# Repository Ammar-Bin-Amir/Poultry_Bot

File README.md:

# Poultry Bot

Poultry Bot is a major technological breakthrough for the poultry industry as it provides solution for utmost problems faced in a poultry farm. The purpose of poultry bot is to completely revolutionize the century old farming practices used till now by introducing the latest technology for 1,190 billion rupees turnover generating sector. The goal is to minimize the biosecurity risk to help improve the production. Further, assisting human to make more informed and better decisions. Poultry bot is an autonomous self-driven robot, monitoring several factors effecting on a poultry farm by implementing ROS and IoT along with LIDAR mapping.

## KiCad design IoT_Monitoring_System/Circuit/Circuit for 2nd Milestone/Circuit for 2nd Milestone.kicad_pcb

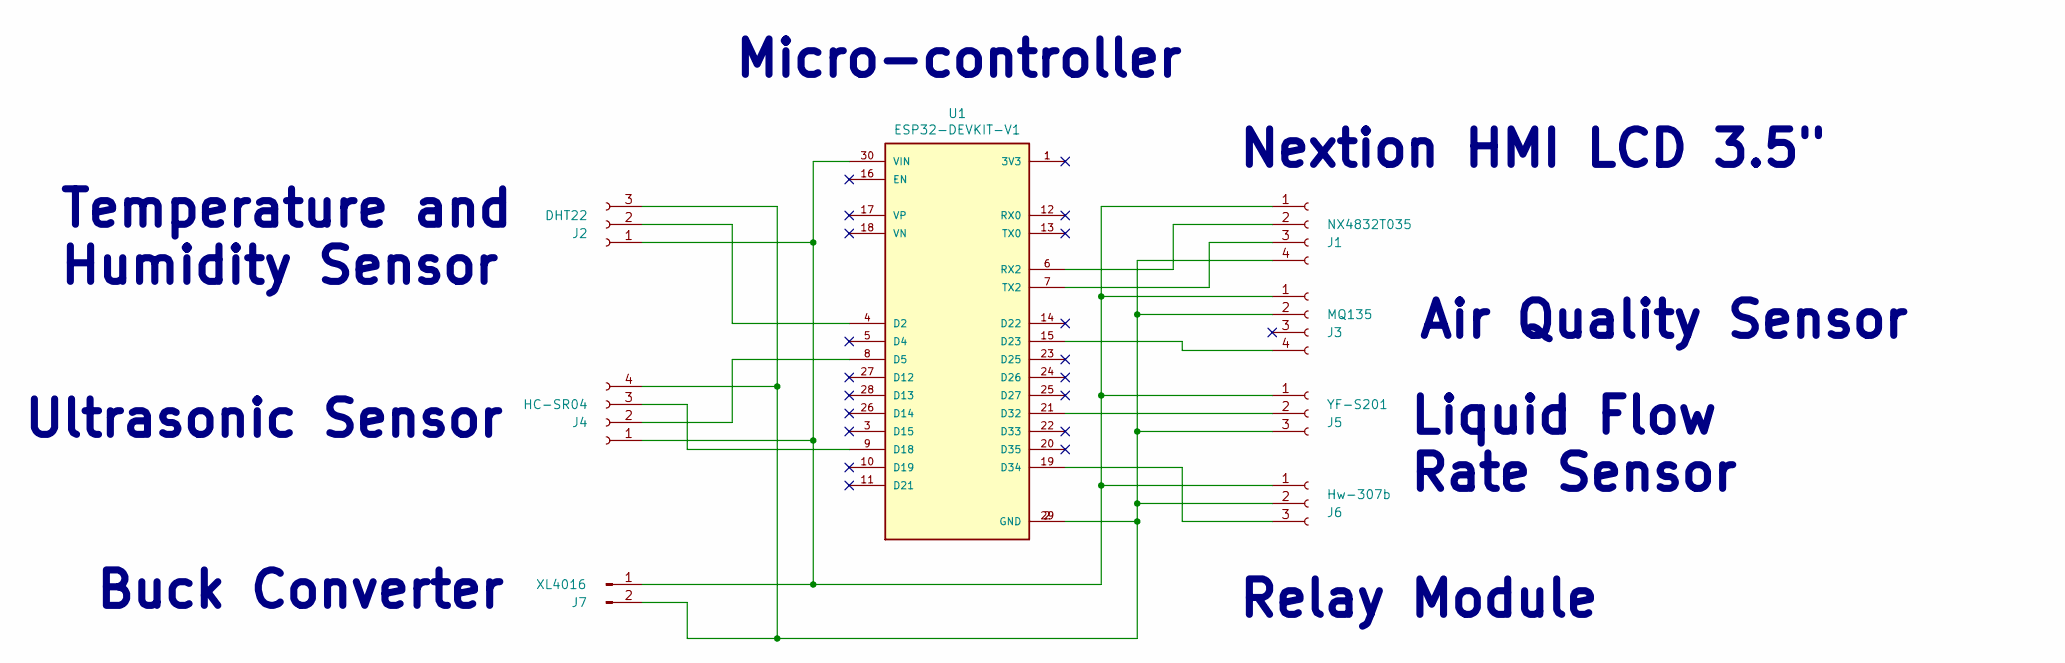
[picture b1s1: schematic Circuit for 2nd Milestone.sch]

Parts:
J1: NX4832T035; PinSocket_1x04_P2.54mm_Vertical
J2: DHT22; PinSocket_1x03_P2.54mm_Vertical
J3: MQ135; PinSocket_1x04_P2.54mm_Vertical
J4: HC-SR04; PinSocket_1x04_P2.54mm_Vertical
J5: YF-S201; PinSocket_1x03_P2.54mm_Vertical
J6: Hw-307b; PinSocket_1x03_P2.54mm_Vertical
J7: XL4016; PinHeader_1x02_P2.54mm_Vertical
U1: ESP32-DEVKIT-V1; MODULE_ESP32_DEVKIT_V1; PARTREV N/A

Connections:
5V: J1.1, J2.1, J3.1, J4.1, J5.1, J6.1, J7.1, U1.30 (VIN)
DHT22: J2.2, U1.4 (D2)
Echo: J4.3, U1.9 (D18)
GND: J1.4, J2.3, J3.2, J4.4, J5.3, J6.2, J7.2, U1.2 (GND), U1.29 (GND)
MQ135: J3.4, U1.15 (D23)
RX: J1.3, U1.7 (TX2)
Relay: J6.3, U1.19 (D34)
TX: J1.2, U1.6 (RX2)
Trigger: J4.2, U1.8 (D5)
YF-S201: J5.2, U1.21 (D32)

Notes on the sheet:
Ultrasonic Sensor
Micro-controller
Relay Module
Liquid Flow Rate Sensor
Air Quality Sensor
Temperature and Humidity Sensor
Nextion HMI LCD 3.5"
Buck Converter

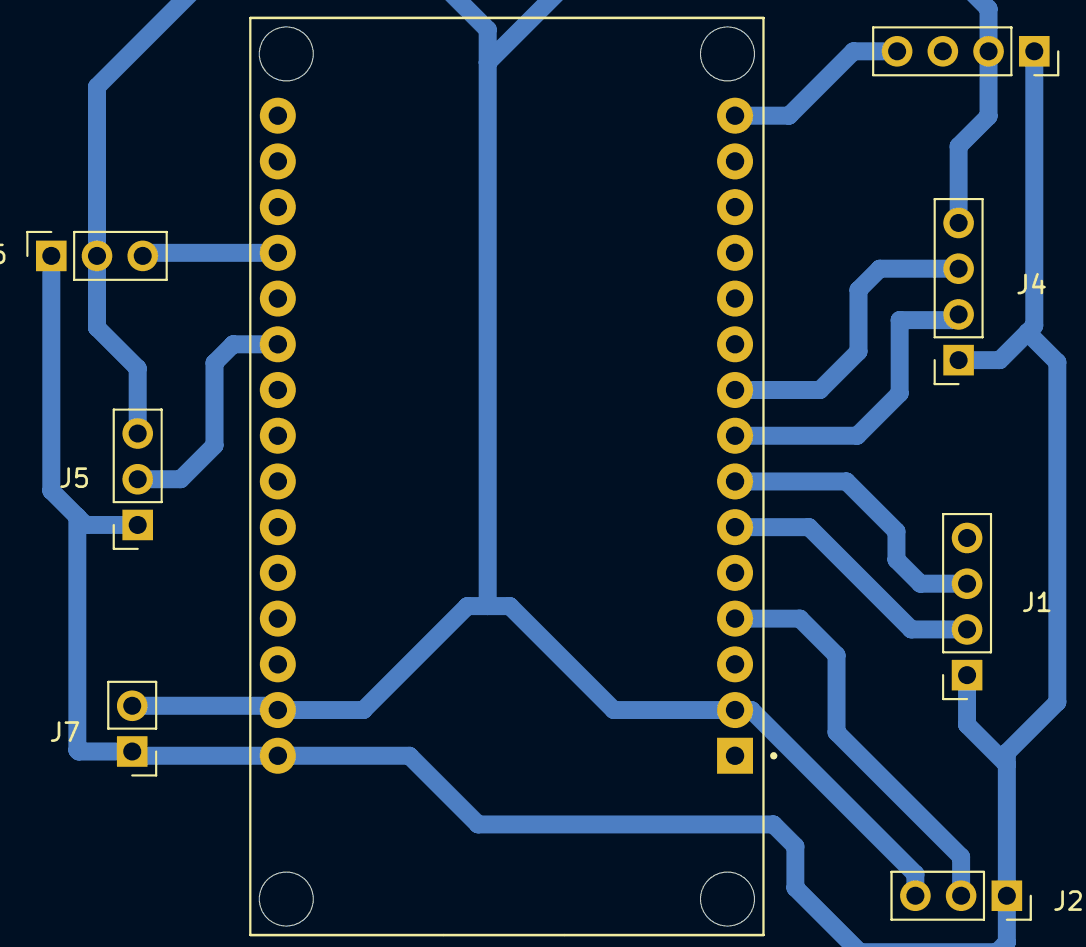
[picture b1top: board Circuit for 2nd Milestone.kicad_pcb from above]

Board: 2 copper layers, 8 parts (0 on the bottom side), 10 nets.

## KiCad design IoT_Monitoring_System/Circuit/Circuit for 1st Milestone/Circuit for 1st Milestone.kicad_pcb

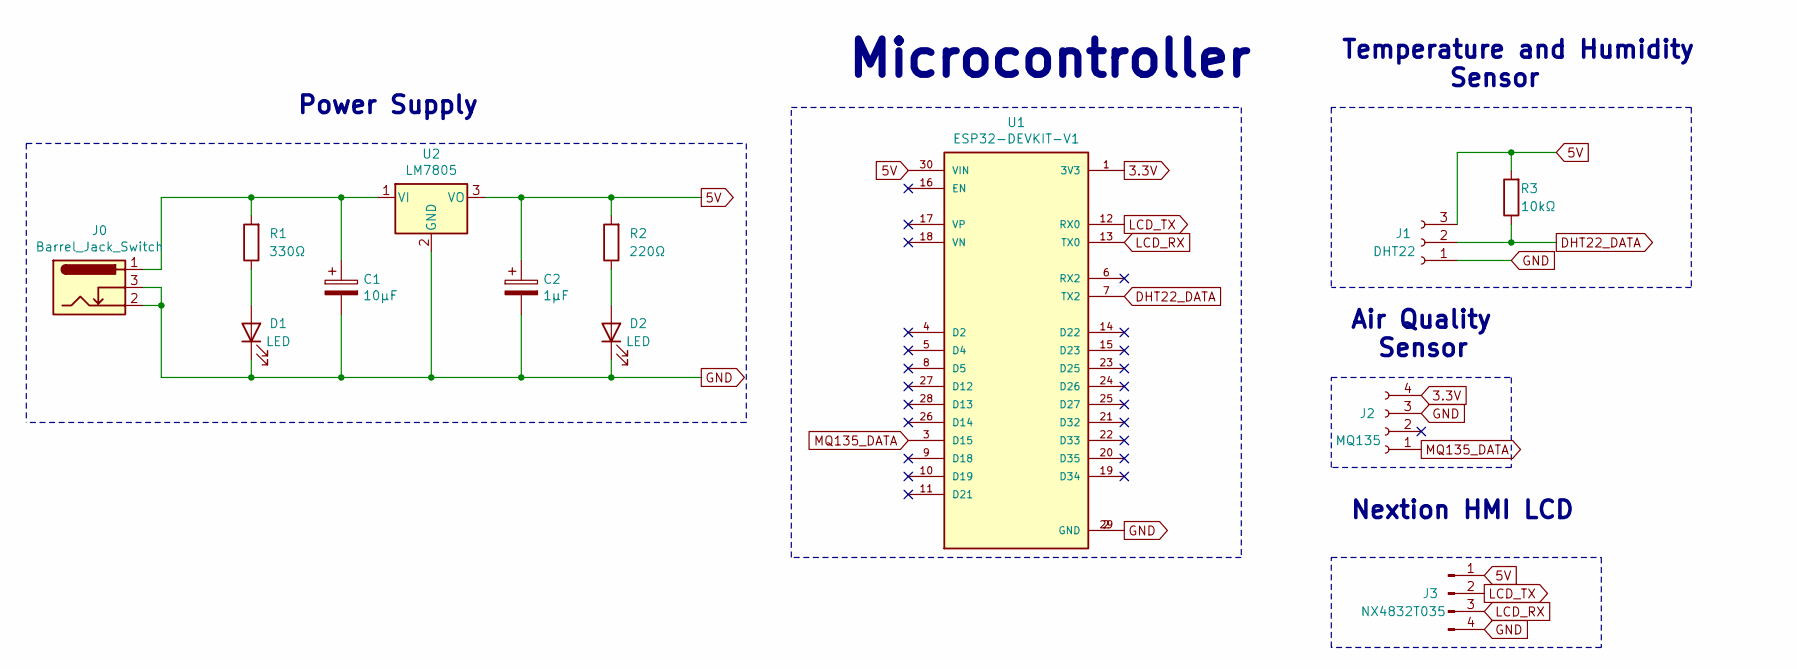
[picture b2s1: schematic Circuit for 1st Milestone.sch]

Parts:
C1: 10μF; CP_Radial_D6.3mm_P2.50mm
C2: 1μF; CP_Radial_D6.3mm_P2.50mm
D1, D2: LED; LED_D5.0mm_Clear
J0: Barrel_Jack_Switch; BarrelJack_Horizontal
J1: DHT22; PinSocket_1x03_P2.54mm_Vertical
J2: MQ135; PinSocket_1x04_P2.54mm_Vertical
J3: NX4832T035; PinHeader_1x04_P2.54mm_Vertical
R1: 330Ω; R_Axial_DIN0207_L6.3mm_D2.5mm_P10.16mm_Horizontal
R2: 220Ω; R_Axial_DIN0207_L6.3mm_D2.5mm_P10.16mm_Horizontal
R3: 10kΩ; R_Axial_DIN0207_L6.3mm_D2.5mm_P10.16mm_Horizontal
U1: ESP32-DEVKIT-V1; MODULE_ESP32_DEVKIT_V1; PARTREV N/A
U2: LM7805; TO-220-3_Vertical

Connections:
3.3V: J2.4, U1.1 (3V3)
5V: C2.1, J1.3, J3.1, R2.2, R3.2, U1.30 (VIN), U2.3 (VO)
DHT22_DATA: J1.2, R3.1, U1.7 (TX2)
GND: C1.2, C2.2, D1.1 (K), D2.1 (K), J0.2, J0.3, J1.1, J2.3, J3.4, U1.2 (GND), U1.29 (GND), U2.2 (GND)
LCD_RX: J3.3, U1.13 (TX0)
LCD_TX: J3.2, U1.12 (RX0)
MQ135_DATA: J2.1, U1.3 (D15)
unnamed: C1.1, J0.1, R1.2, U2.1 (VI)
unnamed: D1.2 (A), R1.1
unnamed: D2.2 (A), R2.1

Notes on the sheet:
Temperature and Humidity Sensor
Air Quality Sensor
Nextion HMI LCD
Power Supply
Microcontroller

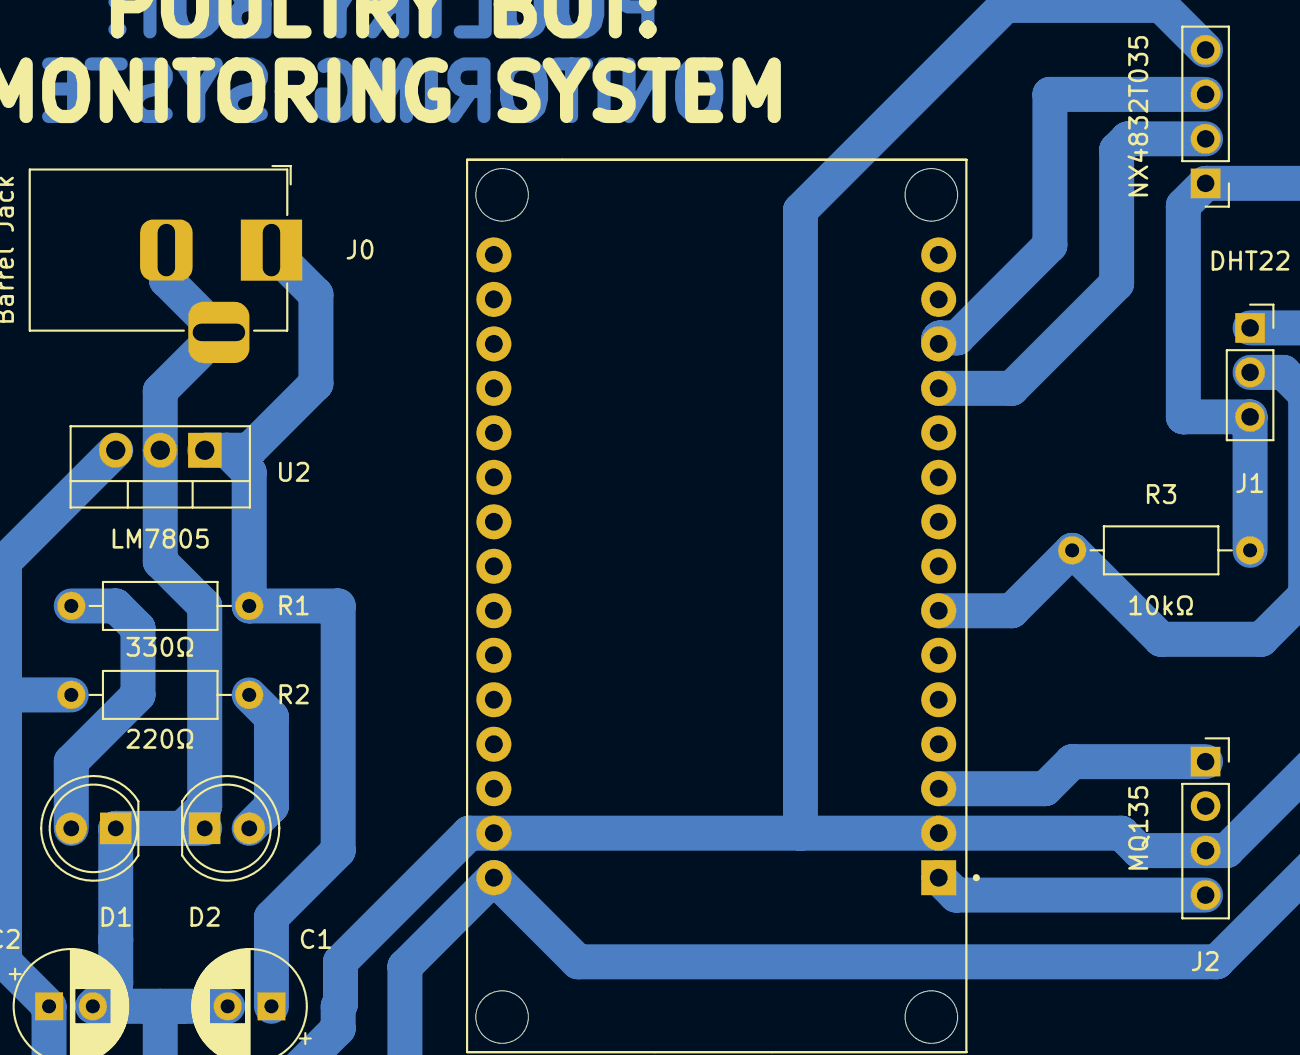
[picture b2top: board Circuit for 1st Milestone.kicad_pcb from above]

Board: 2 copper layers, 13 parts (0 on the bottom side), 10 nets.

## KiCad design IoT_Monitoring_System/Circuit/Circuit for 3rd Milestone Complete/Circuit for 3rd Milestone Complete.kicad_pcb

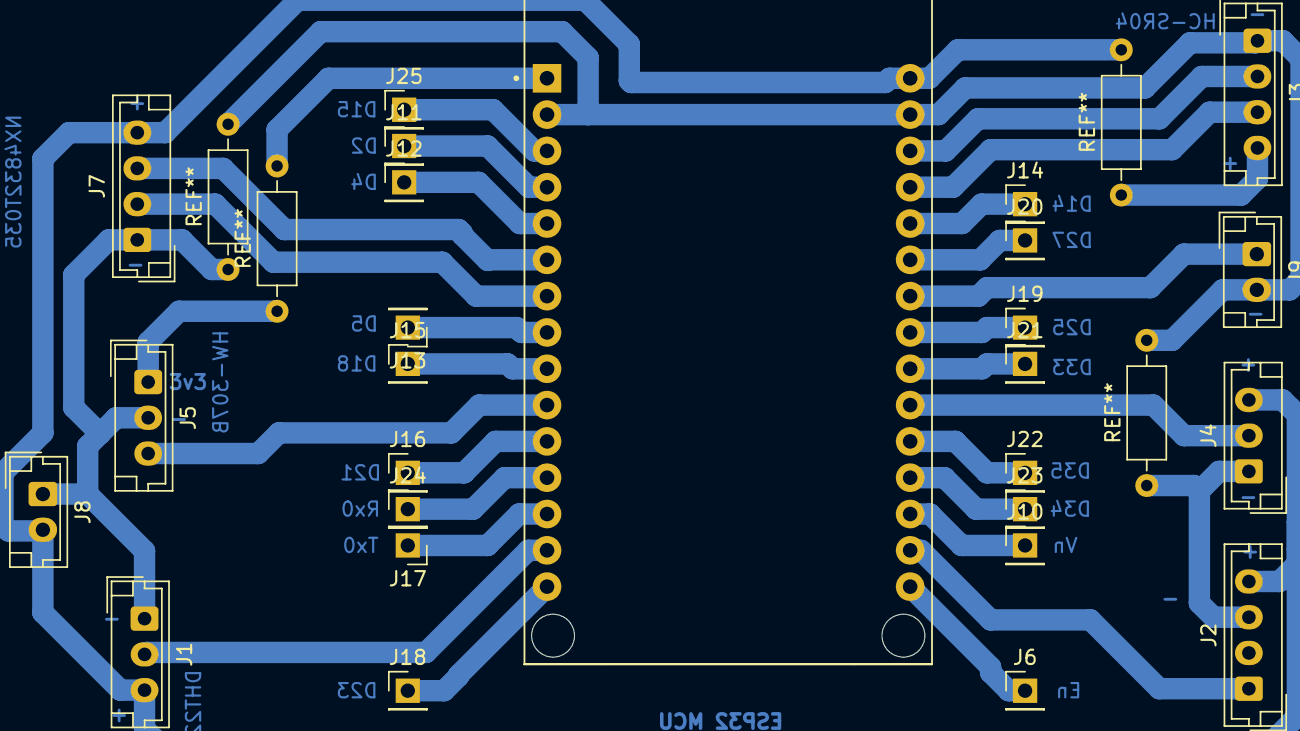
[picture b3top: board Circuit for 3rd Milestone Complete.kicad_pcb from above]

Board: 2 copper layers, 26 parts (0 on the bottom side), 29 nets.

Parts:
J1: DHT22; JST_EH_B3B-EH-A_1x03_P2.50mm_Vertical
J2: MQ135; JST_EH_B4B-EH-A_1x04_P2.50mm_Vertical
J3: HC-SR04; JST_EH_B4B-EH-A_1x04_P2.50mm_Vertical
J4: YF-S201; JST_EH_B3B-EH-A_1x03_P2.50mm_Vertical
J5: HW-307B; JST_EH_B3B-EH-A_1x03_P2.50mm_Vertical
J6: En; PinHeader_1x01_P2.54mm_Vertical
J7: NX4832T035; JST_EH_B4B-EH-A_1x04_P2.50mm_Vertical
J8: XL4016; JST_EH_B2B-EH-A_1x02_P2.50mm_Vertical
J9: Litter Raking; JST_EH_B2B-EH-A_1x02_P2.50mm_Vertical
J10: Vn; PinHeader_1x01_P2.54mm_Vertical
J11: D2; PinHeader_1x01_P2.54mm_Vertical
J12: D4; PinHeader_1x01_P2.54mm_Vertical
J13: D5; PinHeader_1x01_P2.54mm_Vertical
J14: D14; PinHeader_1x01_P2.54mm_Vertical
J15: D18; PinHeader_1x01_P2.54mm_Vertical
J16: D21; PinHeader_1x01_P2.54mm_Vertical
J17: Tx0; PinHeader_1x01_P2.54mm_Vertical
J18: D23; PinHeader_1x01_P2.54mm_Vertical
J19: D25; PinHeader_1x01_P2.54mm_Vertical
J20: D27; PinHeader_1x01_P2.54mm_Vertical
J21: D33; PinHeader_1x01_P2.54mm_Vertical
J22: D35; PinHeader_1x01_P2.54mm_Vertical
J23: D34; PinHeader_1x01_P2.54mm_Vertical
J24: Rx0; PinHeader_1x01_P2.54mm_Vertical
J25: D15; PinHeader_1x01_P2.54mm_Vertical
U1: ESP32 MCU; MODULE_ESP32_DEVKIT_V1

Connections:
unnamed: J2.1, U1.17 (VP)
unnamed: J1.1, J2.3, J3.1, J4.1, J5.2, J7.1, J8.1, J9.2, U1.2 (GND), U1.29 (GND)
unnamed: J1.3, J2.4, J3.4, J4.3, J7.4, J8.2, U1.30 (VIN)
unnamed: J4.2, U1.21 (D32)
unnamed: J5.1, U1.1 (3V3)
unnamed: J25.1, U1.3 (D15)
unnamed: J11.1, U1.4 (D2)
unnamed: J12.1, U1.5 (D4)
unnamed: J7.3, U1.6 (RX2)
unnamed: J7.2, U1.7 (TX2)
unnamed: J13.1, U1.8 (D5)
unnamed: J15.1, U1.9 (D18)
unnamed: J5.3, U1.10 (D19)
unnamed: J16.1, U1.11 (D21)
unnamed: J24.1, U1.12 (RX0)
unnamed: J17.1, U1.13 (TX0)
unnamed: J1.2, U1.14 (D22)
unnamed: J18.1, U1.15 (D23)
unnamed: J6.1, U1.16 (EN)
unnamed: J10.1, U1.18 (VN)
unnamed: J23.1, U1.19 (D34)
unnamed: J22.1, U1.20 (D35)
unnamed: J21.1, U1.22 (D33)
unnamed: J19.1, U1.23 (D25)
unnamed: J9.1, U1.24 (D26)
unnamed: J20.1, U1.25 (D27)
unnamed: J14.1, U1.26 (D14)
unnamed: J3.3, U1.27 (D12)
unnamed: J3.2, U1.28 (D13)

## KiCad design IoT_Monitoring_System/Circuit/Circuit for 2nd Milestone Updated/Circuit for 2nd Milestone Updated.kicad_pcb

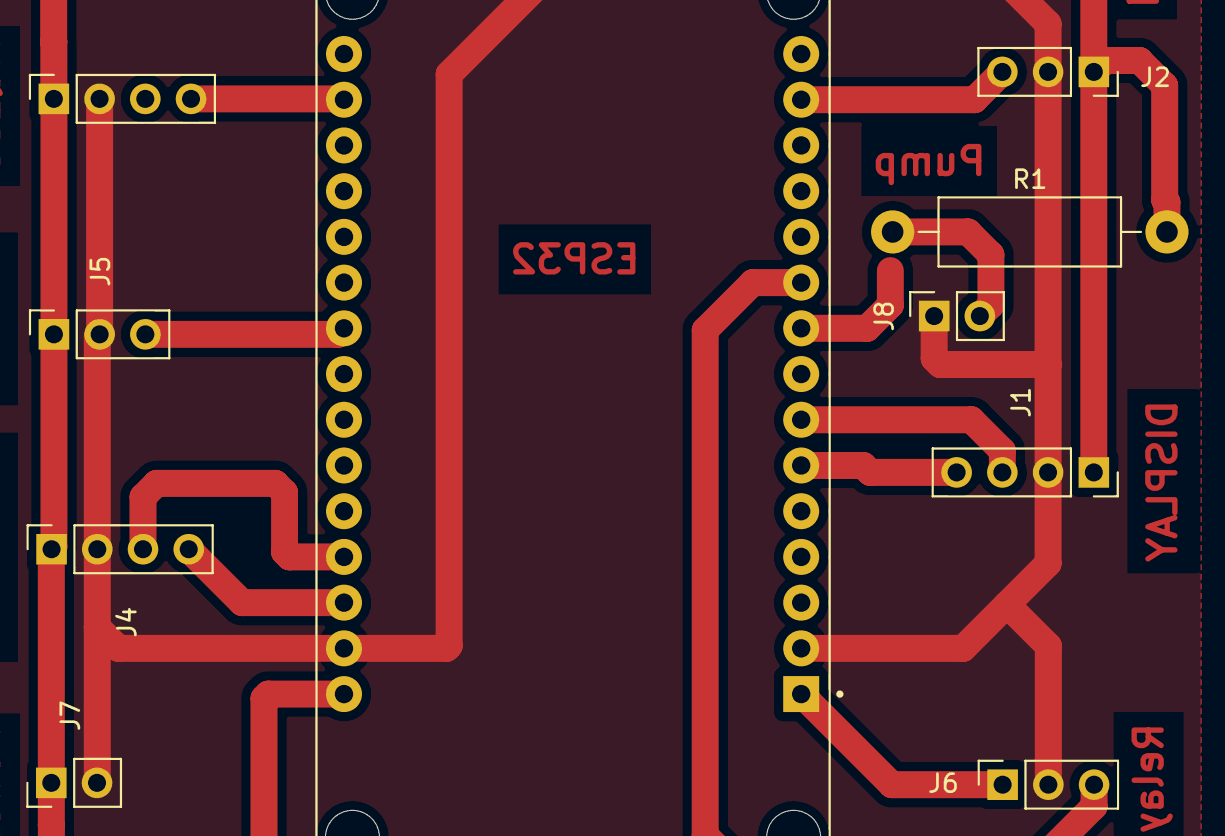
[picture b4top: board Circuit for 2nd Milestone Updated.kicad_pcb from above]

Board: 2 copper layers, 10 parts (0 on the bottom side), 7 nets.

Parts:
J1: NX4832T035; PinSocket_1x04_P2.54mm_Vertical
J2: DHT22; PinSocket_1x03_P2.54mm_Vertical
J3: MQ135; PinSocket_1x04_P2.54mm_Vertical
J4: HC-SR04; PinSocket_1x04_P2.54mm_Vertical
J5: YF-S201; PinSocket_1x03_P2.54mm_Vertical
J6: Hw-307b; PinSocket_1x03_P2.54mm_Vertical
J7: XL4016; PinHeader_1x02_P2.54mm_Vertical
J8: Pump Input; PinSocket_1x02_P2.54mm_Vertical
R1: R; R_Axial_DIN0411_L9.9mm_D3.6mm_P15.24mm_Horizontal
U1: ESP32-DEVKIT-V1; MODULE_ESP32_DEVKIT_V1

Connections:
unnamed: J1.1, J2.1, J3.1, J4.1, J5.1, J7.1, R1.2
unnamed: J1.2, J2.2, J3.2, J4.2, J5.2, J6.2, J7.2, J8.1
unnamed: U1.2 (GND), U1.29 (GND)
unnamed: J3.4, U1.17 (VP)
unnamed: J6.1, U1.1 (3V3)
unnamed: J6.3, U1.10 (D19)
unnamed: J8.2, R1.1

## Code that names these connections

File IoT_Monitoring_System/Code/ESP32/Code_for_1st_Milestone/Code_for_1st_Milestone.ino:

#include <WiFi.h>
#include <WiFiClient.h>
#include <BlynkSimpleEsp32.h>


#define BLYNK_TEMPLATE_ID "TMPLqo4MJG8x"
#define BLYNK_DEVICE_NAME "IoT"
#define BLYNK_AUTH_TOKEN "gkp3KEPrshlwgZ00bzexG33Jd64ayy_U"

char ssid[]= "B-94";
char pass[]= "d24b687c";


#include "DHT.h"
#include "MQUnifiedsensor.h"// MQ135 Enable
// #include <SoftwareSerial.h>
#include <HardwareSerial.h>

#ifndef ESP32
#pragma message(THIS EXAMPLE IS FOR ESP32 ONLY!)
#error Select ESP32 board.
#endif

//Definitions
#define dhtPin 17
#define DHTTYPE DHT22
#define mqPin 36
#define lcd_tx 1 //tx0
#define lcd_rx 3 //rx0
#define litter 16 //rx2
#define pump 15 //d15
#define valve 02 //d2

#define board ("ESP-32")          // Development Board
#define Voltage_Resolution 3.3    // VCC
#define pin 15                    // Analog Input 0 of ESP32
#define type "MQ-135"             // MQ135
#define ADC_Bit_Resolution 12     // For ESP32
#define RatioMQ135CleanAir 3.6    // RS / R0 = 3.6 ppm

MQUnifiedsensor MQ135(board, Voltage_Resolution, ADC_Bit_Resolution, pin, type);
DHT dht(dhtPin, DHTTYPE);

float NH4 = 3;
int h, t, nh;
unsigned long prevTime = 0;

void setup(void){
  Serial.begin(9600);
  // mySerial.begin(115200);

//Set math model to calculate the PPM concentration and the value of constants
  MQ135.setRegressionMethod(1); //_PPM =  a*ratio^b
  MQ135.setA(110.47); MQ135.setB(-2.862); // Configure the equation to to calculate C02 concentration
  dht.begin();
    /*
    Exponential regression:
  GAS      | a      | b
  CO       | 605.18 | -3.937  
  Alcohol  | 77.255 | -3.18 
  CO2      | 110.47 | -2.862
  Toluen   | 44.947 | -3.445
  NH4      | 102.2  | -2.473
  Aceton   | 34.668 | -3.369
  */
  
  MQ135.init(); 
  Serial.print("Calibrating please wait.");
  float calcR0 = 0;
  for(int i = 1; i<=10; i ++)
  {
    MQ135.update(); // Update data, the arduino will read the voltage from the analog pin
    calcR0 += MQ135.calibrate(RatioMQ135CleanAir);
    Serial.print(".");
  }
  MQ135.setR0(calcR0/10);
  // Serial.println("  done!.");
  
  if(isinf(calcR0)) {Serial.println("Warning: Conection issue, R0 is infinite (Open circuit detected) please check your wiring and supply"); while(1);}
  if(calcR0 == 0){Serial.println("Warning: Conection issue found, R0 is zero (Analog pin shorts to ground) please check your wiring and supply"); while(1);}
  MQ135.serialDebug(true);
  MQ135.setA(102.2); MQ135.setB(-2.473); // Configure the equation to to calculate NH4 concentration

  Blynk.begin(BLYNK_AUTH_TOKEN, ssid, pass, "blynk.cloud", 80);
  Blynk.run();

  delay(1000);
}

void loop(void){
  unsigned long currentTime = millis();
  if(currentTime-prevTime >= 3000){
      prevTime = currentTime - millis();
      if(NH4 == 3){
        NH4 = 4;
      }
      else if(NH4 == 4){
        NH4 = 3;
      }
  }
  MQ135.update(); // Update data, the arduino will read the voltage from the analog pin
  MQ135.readSensor(); // Sensor will read PPM concentration using the model, a and b values set previously or from the setup
  NH4 = MQ135.ppmprint(1);
  delay(150);
  h = dht.readHumidity();
  t = dht.readTemperature();
  Blynk.virtualWrite(V0, t);
  Blynk.virtualWrite(V1, h);
  Blynk.virtualWrite(V2,nh);
  //temprature page
Serial.print("n1.val=");
  Serial.print(t);
Serial.write(0xff);
Serial.write(0xff);
Serial.write(0xff);
  // float bar = 100*(t/125+4);
  Serial.print("j1.val=");
  Serial.print(t);
Serial.write(0xff);
Serial.write(0xff);
Serial.write(0xff);
//humidity page
Serial.print("n2.val=");
  Serial.print(h);
Serial.write(0xff);
Serial.write(0xff);
Serial.write(0xff);
Serial.print("j2.val=");
  Serial.print(h);
Serial.write(0xff);
Serial.write(0xff);
Serial.write(0xff);
//Ammonia Page
Serial.print("n3.val=");
nh=NH4;
  Serial.print(nh);
Serial.write(0xff);
Serial.write(0xff);
Serial.write(0xff);


}

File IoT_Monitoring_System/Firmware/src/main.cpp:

#include <Arduino.h>
#include "DHT.h"
#include "EasyNextionLibrary.h"
#include "WiFi.h"
#include "ThingSpeak.h" 
#include <HTTPClient.h>
#include <FlowSensor.h>
#include <NewPing.h>

// put pin definitions here
const int dhtPin = 22;
const int mqPin = 36; //vp
const int pumpPin = 19;
const int pumpInput = 18;
const int flowSensorPin = 33;
const int trigger = 12;
const int echo = 13;
int pumpStatus = 1;

// Constants
#define WIFI_TIMEOUT_MS 2000
#define WIFI_NETWORK "EVO-Charji-7404"
#define WIFI_PASSWORD "BSJ5vr5M"
// #define WIFI_NETWORK "B-94"
// #define WIFI_PASSWORD "d24b687c"
#define CHANNELID 2047728 //2184577
#define APIKEY "PKNGA4A9TABT1FN2" //"33WFVMB4KNV4QM8Z"
#define MAX_DISTANCE 60 //cm

// Struct declarations
DHT dht(dhtPin, DHT22);
EasyNex myDisplay(Serial2); 
WiFiClient client;
FlowSensor Sensor(YFS201, flowSensorPin);
NewPing sonar(trigger, echo, MAX_DISTANCE); // NewPing setup of pins and maximum distance.

//variables under monitoring
float humidity, temperature, flowRate, distance;
int intTemp;
int mqVoltage, ammoniaPPB, ammoniaPPM;
unsigned long lastPrintTime = 1000;
unsigned long lastDisplayUpdate = 1000;
unsigned long lastUpdateTemp = 1000;
unsigned long lastUpdateHumidity = 2000;
unsigned long lastUpdateAmmonia= 3000;
unsigned long lastUpdateLiquid= 4000;
unsigned long lastUpdateFlow= 5000;
unsigned long lastUpdateBattery =6000;
unsigned long lastUpdateWifi =60000;
unsigned long timebefore = 0; // Same type as millis() for pump reading
String stringFromNextion;

// put function declarations here:
void count()
{
	Sensor.count();
}

// void pumpOn(){
//   digitalWrite(pumpPin, !pumpStatus);
//   pumpStatus = !pumpStatus;
// }

void connectWifi(){
  Serial.println("Connecting to Wifi");
  WiFi.mode(WIFI_STA);
  WiFi.begin(WIFI_NETWORK, WIFI_PASSWORD);
  unsigned long startAttemptTime = millis();
  
  while(WiFi.status()!= WL_CONNECTED && (millis()-startAttemptTime) <= WIFI_TIMEOUT_MS){
    Serial.print(".");
    delay(200);
  }

  if(WiFi.status() != WL_CONNECTED){
    Serial.println("Failed to connect wifi");
  }
  else{
    Serial.println("Connection Successfull");
    Serial.println(WiFi.localIP());
  }
}

//Main Functions

void setup() {
  delay(1000);
  Serial.begin(115200);
  Serial2.begin(9600);
  pinMode(pumpPin, OUTPUT);
  connectWifi();
  Sensor.begin(count);
  lastPrintTime = millis();
  ThingSpeak.begin(client);
  myDisplay.writeNum("n0.val", 0);
  delay(3000);
}

void loop() {
  //pump
  int num = myDisplay.readNumber("n0.val");
      if (num == 1) {
      Serial.println("Turn PUMP ON");
      digitalWrite(pumpPin, LOW);
      myDisplay.writeNum("n0.val", 1);
    }
    else if (num == 0) {
      Serial.println("Turn PUMP OFF");
      myDisplay.writeNum("n0.val", 0);
      digitalWrite(pumpPin, HIGH);
    }
  

  if (millis() - timebefore >= 1000)
	{
		Sensor.read();
		Serial.print("Flow rate (L/minute) : ");
    flowRate = Sensor.getFlowRate_m();
		Serial.println(flowRate);
		timebefore = millis();
    delay(50);                     // Wait 50ms between pings (about 20 pings/sec). 29ms should be the shortest delay between pings.
    Serial.print("Ping: ");
    distance = sonar.ping_cm();
    Serial.print(distance); // Send ping, get distance in cm and print result (0 = outside set distance range)
    Serial.println("cm");
	}

  if(millis()-lastDisplayUpdate >= 2000){
    humidity = dht.readHumidity();
    temperature = dht.readTemperature();

    mqVoltage = analogRead(mqPin);
    ammoniaPPB = map(mqVoltage,0, 4095, 0, 500);
    ammoniaPPM = ammoniaPPB/10;

    Serial.println("===========================");
    Serial.print("Humidity = ");
    Serial.println(humidity);
    Serial.print("temp = ");
    Serial.println(temperature);
    Serial.print("MQ Voltage = ");
    Serial.println(mqVoltage);
    Serial.println("===========================");

    //writing on display
    Serial.println("Updating Display");
    myDisplay.writeNum("n1.val", temperature);
    myDisplay.writeNum("n2.val", humidity);
    myDisplay.writeNum("n3.val", ammoniaPPM);
    //distance query here
    myDisplay.writeStr("t4.txt", "HIGH");

    myDisplay.writeNum("x5.val", flowRate);
    myDisplay.writeNum("n6.val", 34);
    lastDisplayUpdate = millis();
  }
  //dashboard update
  if(millis()-lastUpdateAmmonia >= 20000){
    Serial.println("Updating Dashboard");
    ThingSpeak.setField(1, temperature);
    ThingSpeak.setField(2, humidity);
    ThingSpeak.setField(3, ammoniaPPM);
    if(distance >= 40)
    ThingSpeak.setField(4, distance);
    ThingSpeak.setField(5, flowRate);
    ThingSpeak.setField(6, ammoniaPPM);
    ThingSpeak.writeFields(CHANNELID, APIKEY);
    lastUpdateAmmonia = millis();
  }
}

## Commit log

2023-11-26 Added IoT Report Book
2023-11-26 Deleted IoT Report Book
2023-11-26 Added IoT Research Paper
2023-11-26 Added ROS Research Paper
2023-11-26 Added Bot Pics
2023-11-26 Added Poultry Farm Visit Videos
2023-11-26 Added Display Unit
2023-11-26 Added Remote Control App
2023-11-26 Added Bot Structure
2023-11-26 Changed Robot Structure Path
2023-11-26 Added IoT Videos
2023-11-27 inserted Book
2023-11-27 code uploaded
2023-11-27 firmware files
2023-11-27 Robot_working
2023-11-27 videos uploaded
2023-11-27 Testing Videos
2024-02-25 Add HMI UI files
2024-02-25 Add firmware
    Firmware of Monitoring Controller and ESP Camera
2024-02-25 Add circuit files for 1st, 2nd and 3rd milestones
2024-02-25 Remove unwanted file
2024-02-25 Remove unwanted files
2024-02-25 Add circuit files
